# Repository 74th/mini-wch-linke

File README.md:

# MINI WCH-LinkE

WCH-LinkE Clone

- Shop Site: [BOOTH](https://74th.booth.pm/items/5022813)

## Features

- Arduino UNO R4-like SWD with UART 1.26mm 10-pin added. VCC is 3.3V.
- USB Type-C

## v1.1.1

- semantics: [PDF](documents/mini-wch-linke-v1.1.1.pdf) [kicanvas](https://kicanvas.org/?github=https%3A%2F%2Fgithub.com%2F74th%2Fmini-wch-linke%2Fblob%2F1.1.1%2Fwch-link.kicad_sch)
- pcb: [kicanvas](https://kicanvas.org/?github=https%3A%2F%2Fgithub.com%2F74th%2Fmini-wch-linke%2Fblob%2F1.1.1%2Fwch-link.kicad_pcb)

### BOM

| Reference | Name | Quantity |
| --- | --- | --- |
| C1, C3 | Capacitor 0603 22pF | 2 |
| C2, C4, C6, C7 | Capacitor 0603 10uF | 4 |
| C5 | Capacitor 0603 100nF | 1 |
| CH4 | Pin Header 2x5 Pitch 2.54mm | 1 |
| D1 | LED 0805 BLUE | 1 |
| D2 | LED 0805 RED | 1 |
| J1 | USB Type-C Receptacle - USB | 1 |
| J2 | Box Pin Header 2x5 Pitch 1.27mm | 1 |
| R1, R2, R5, R6 | Register 0603 100Ω | 4 |
| R3, R4 | Register 0603 270Ω | 2 |
| R7, R8 | Register 0603 1kΩ | 2 |
| R9, R10 | Register 0603 10kΩ | 2 |
| R11, R12 | Register 0603 5.1kΩ | 2 |
| SW1 | Button SKRPABE010 | 1 |
| U1 | Regulator 3.3V SOT-223 AMS1117-3.3 | 1 |
| U2 | MCU LQFP48 WCH CH32V305FBP6 | 1 |
| Y1 | Crystal 3225 12MHz | 1 |

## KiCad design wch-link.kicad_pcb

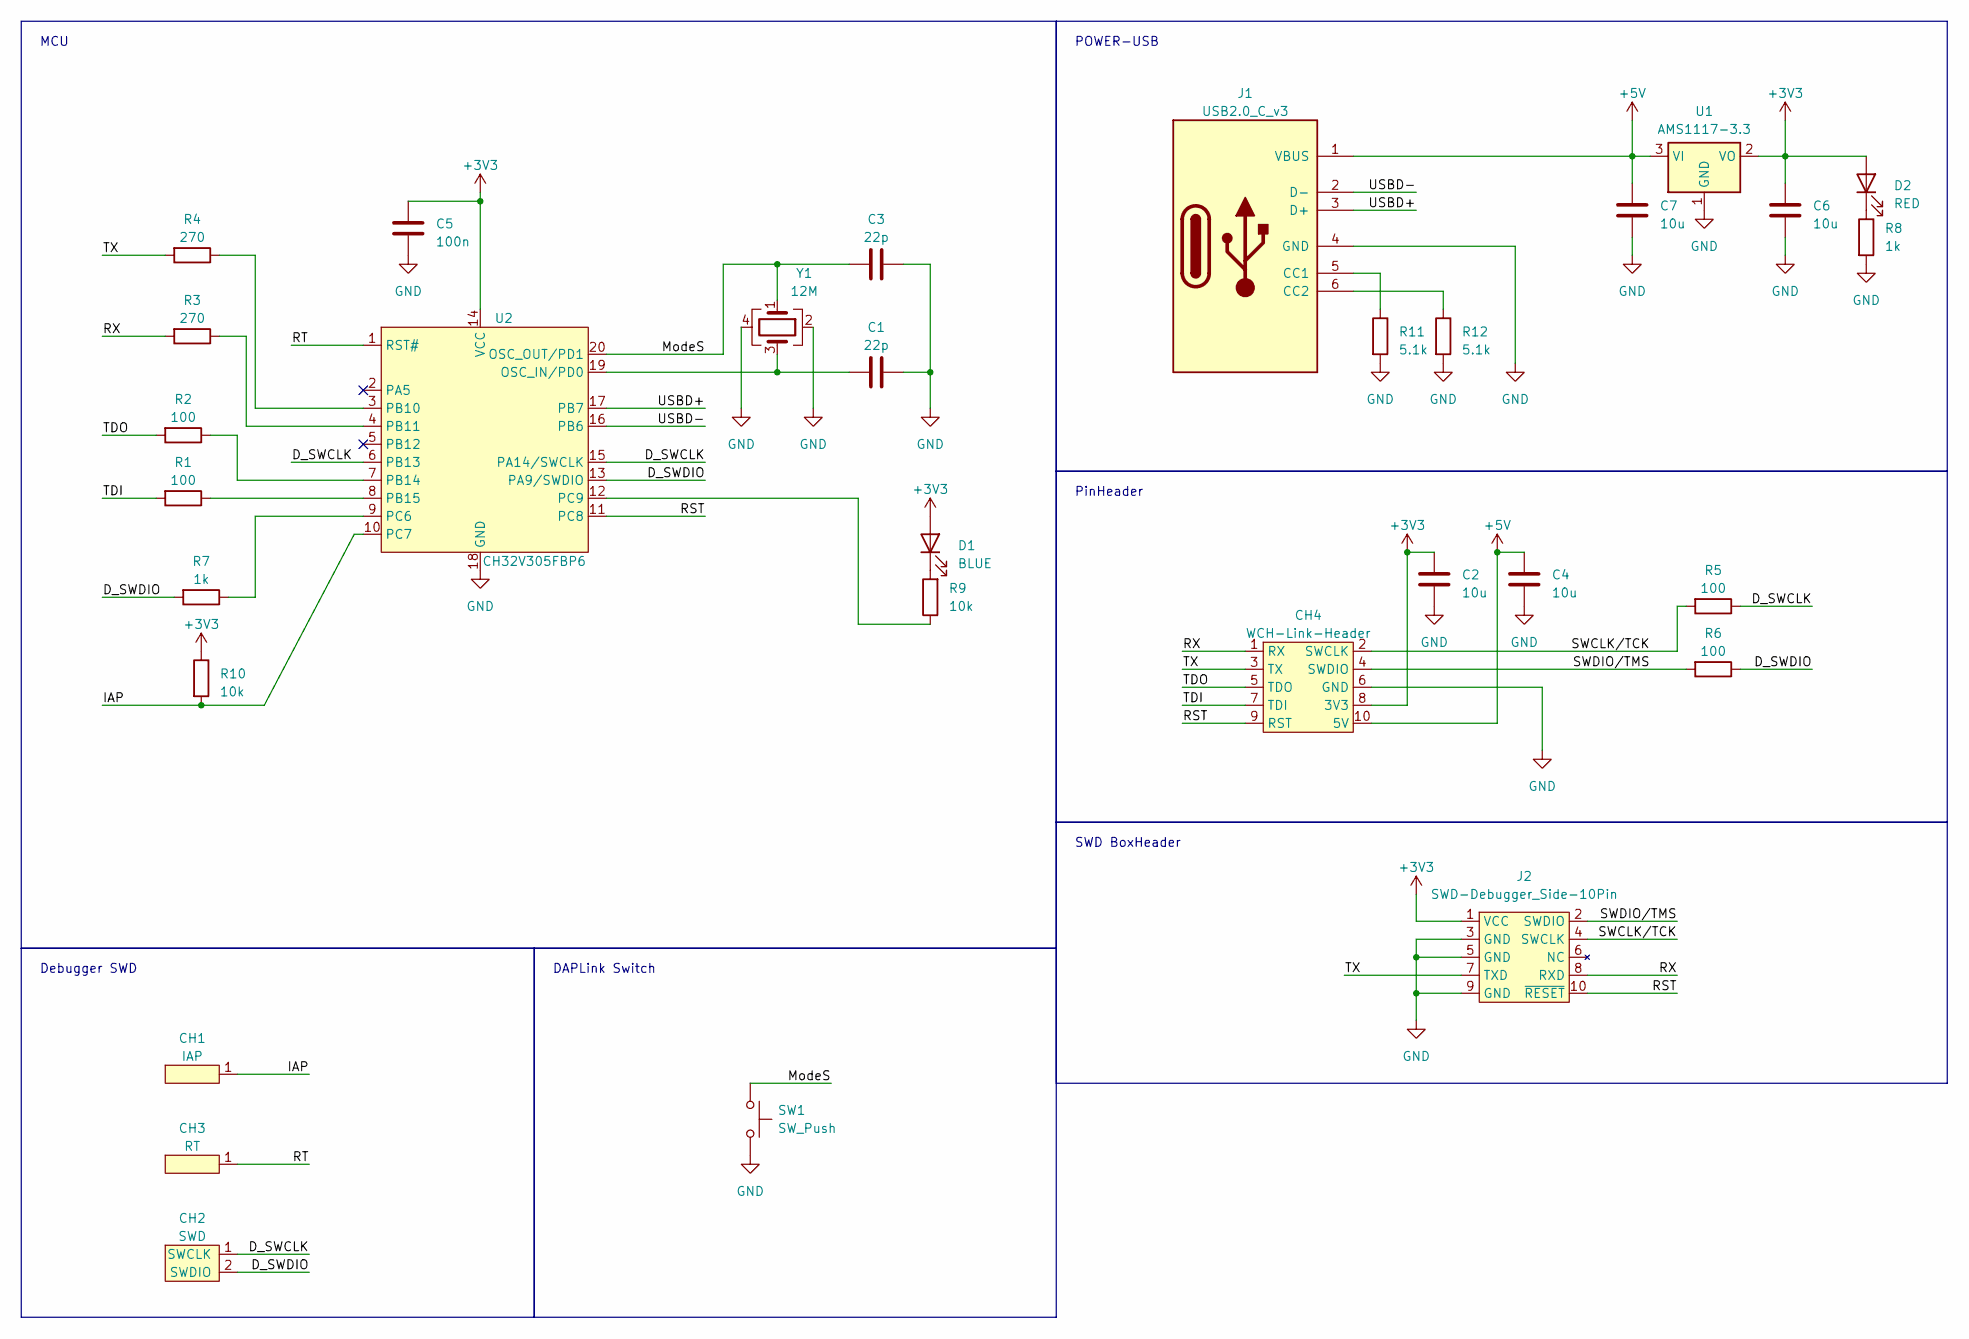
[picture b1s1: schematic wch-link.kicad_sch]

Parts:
C1, C3: 22p; Capacitor_0603_1608
C2, C4, C6, C7: 10u; Capacitor_0603_1608
C5: 100n; Capacitor_0603_1608
CH1: IAP; 1Pin
CH2: SWD; 2Pin
CH3: RT; 1Pin
CH4: WCH-Link-Header; Side-2x5P-PinHeader-Right
D1: BLUE; LED_0805_2012Metric_Pad1.15x1.40mm_HandSolder
D2: RED; LED_0805_2012Metric_Pad1.15x1.40mm_HandSolder
J1: USB2.0_C_v3; USB-C-12-Pin-SMD
J2: SWD-Debugger_Side-10Pin; BoxPinHeader_2x05_P1.27mm_Vertical
R1, R2, R5, R6: 100; Register_0603_1608
R3, R4: 270; Register_0603_1608
R7, R8: 1k; Register_0603_1608
R9, R10: 10k; Register_0603_1608
R11, R12: 5.1k; Register_0603_1608
SW1: SW_Push; SKRPABE010
U1: AMS1117-3.3; SOT-223-3_TabPin2
U2: CH32V305FBP6; TSSOP-20_4.4x6.5mm_P0.65mm
Y1: 12M; Crystal_SMD_3225-4Pin_3.2x2.5mm_HandSoldering

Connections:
+3V3: C2.2, C5.1, C6.1, CH4.8 (3V3), D1.2 (A), D2.2 (A), J2.1 (VCC), R10.1, U1.2 (VO), U2.14 (VCC)
+5V: C4.2, C7.1, CH4.10 (5V), J1.1 (VBUS), U1.3 (VI)
/D_SWCLK: CH2.1 (SWCLK), R5.1, U2.6 (PB13), U2.15 (PA14/SWCLK)
/D_SWDIO: CH2.2 (SWDIO), R6.1, R7.2, U2.13 (PA9/SWDIO)
/IAP: CH1.1, R10.2, U2.10 (PC7)
/ModeS: C3.2, SW1.1, U2.20 (OSC_OUT/PD1), Y1.1
/RST: CH4.9 (RST), J2.10 (~RESET), U2.11 (PC8)
/RT: CH3.1, U2.1 (RST#)
/RX: CH4.1 (RX), J2.8 (RXD), R3.2
/SWCLK/TCK: CH4.2 (SWCLK), J2.4 (SWCLK), R5.2
/SWDIO/TMS: CH4.4 (SWDIO), J2.2 (SWDIO), R6.2
/TDI: CH4.7 (TDI), R1.2
/TDO: CH4.5 (TDO), R2.2
/TX: CH4.3 (TX), J2.7 (TXD), R4.2
/USBD+: J1.3 (D+), U2.17 (PB7)
/USBD-: J1.2 (D-), U2.16 (PB6)
GND: C1.1, C2.1, C3.1, C4.1, C5.2, C6.2, C7.2, CH4.6 (GND), J1.4 (GND), J2.3 (GND), J2.5 (GND), J2.9 (GND), R8.2, R11.2, R12.2, SW1.2, U1.1 (GND), U2.18 (GND), Y1.2, Y1.4
unnamed: D1.1 (K), R9.2
unnamed: D2.1 (K), R8.1
unnamed: J1.5 (CC1), R11.1
unnamed: J1.6 (CC2), R12.1
unnamed: C1.2, U2.19 (OSC_IN/PD0), Y1.3
unnamed: R4.1, U2.3 (PB10)
unnamed: R3.1, U2.4 (PB11)
unnamed: R2.1, U2.7 (PB14)
unnamed: R1.1, U2.8 (PB15)
unnamed: R7.1, U2.9 (PC6)
unnamed: R9.1, U2.12 (PC9)

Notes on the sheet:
SWD BoxHeader
PinHeader
Debugger SWD
MCU
DAPLink Switch
POWER-USB

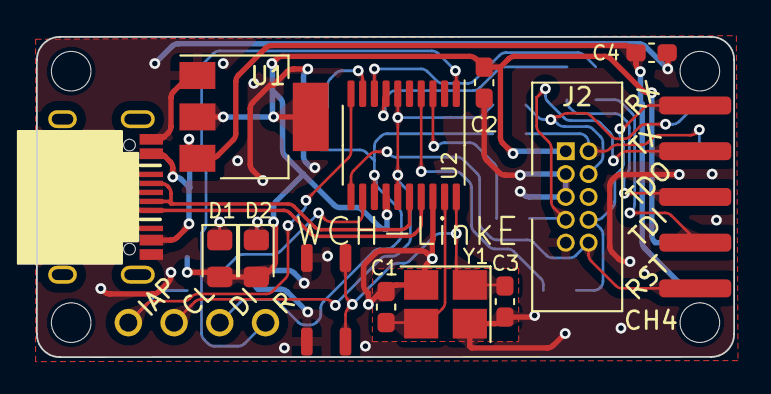
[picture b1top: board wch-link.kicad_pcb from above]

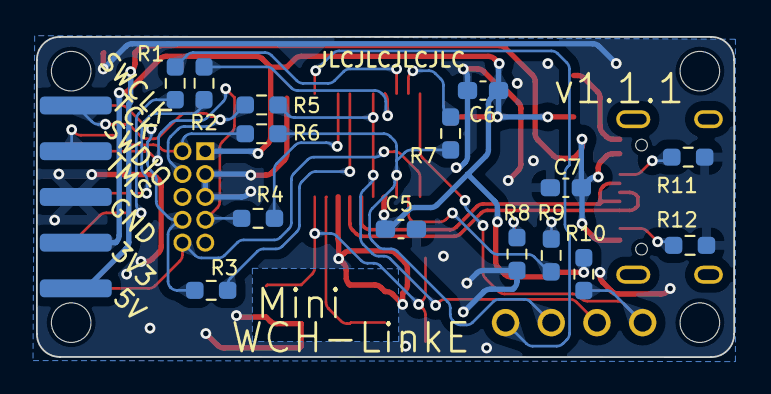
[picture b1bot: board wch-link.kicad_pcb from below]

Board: 2 copper layers, 38.7 x 17.8 mm, 35 parts (15 on the bottom side), 28 nets.

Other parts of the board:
M1, M2, M3, M4: M2-Hole

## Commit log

2023-07-12 v1.1.0
2023-08-20 v1.1.1
2023-09-20 update docuemnts
